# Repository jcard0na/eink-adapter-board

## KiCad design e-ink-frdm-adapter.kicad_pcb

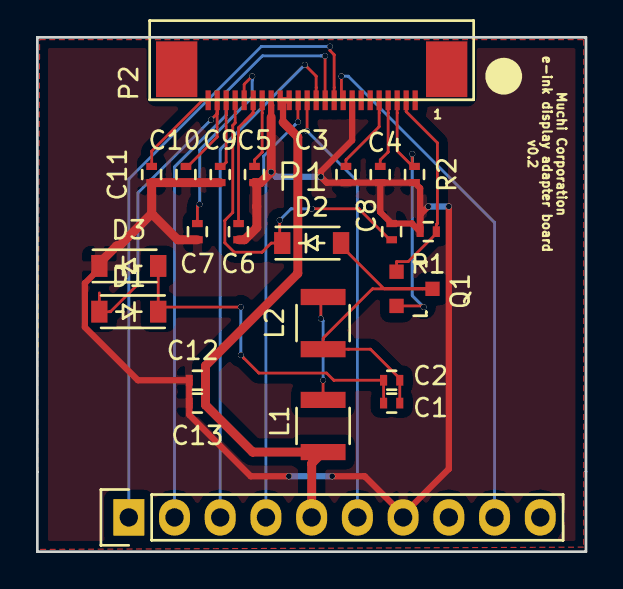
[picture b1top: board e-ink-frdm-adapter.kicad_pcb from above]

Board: 2 copper layers, 30.5 x 28.6 mm, 23 parts (0 on the bottom side), 22 nets.

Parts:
C1, C2, C3, C4, C5, C6, C7, C8, C9, C10, C11, C12, C13: MF-CAP-0402-1uF; R_0402
D1, D2, D3: MF-DIO-SOD123-BAT42; SOD-123
L1, L2: MF-IND-1210-10uH; R_1210
P1: 2-1734839-4; TE-2-1734592-4-bottom_contact
P2: 68000-110HLF; Pin_Header_Straight_1x10
Q1: MF-DSC-SOT233-BSS138; SOT-23
R1: MF-RES-0402-10K; R_0402
R2: MF-RES-0402-0; R_0402

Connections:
/BUSY: P1.9, P2.9
/CS: P1.12, P2.3
/D/~C: P1.11, P2.2
/GDR: P1.2, Q1.1, R1.1
/PREVGH: C8.1, D2.1, P1.21
/PREVGL: C10.1, D1.2, P1.23
/RESE: P1.3, Q1.2, R2.1
/SCLK: P1.13, P2.6
/SDI: P1.14, P2.4
/V3.3: C12.1, C13.1, L1.2, P1.15, P1.16, P2.5
/~RESET: P1.10, P2.1
GND: C3.1, C4.2, C5.2, C6.2, C7.2, C8.2, C9.2, C10.2, C11.2, C12.2, C13.2, D3.1, P1.8, P1.17, P2.7, R1.2, R2.2
unnamed: C1.1, C2.1, D1.1, D3.2
unnamed: C1.2, C2.2, D2.2, L2.1, Q1.3
unnamed: C3.2, P1.5
unnamed: C4.1, P1.4
unnamed: C5.1, P1.18
unnamed: C6.1, P1.19
unnamed: C7.1, P1.20
unnamed: C9.1, P1.22
unnamed: C11.1, P1.24
unnamed: L1.1, L2.2

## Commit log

2016-07-16 Regen netlist
2016-07-16 These files should be ignored
2016-08-12 Use bottom contact FPC conn footprint
2016-08-15 1. P1 FPC connector changed from top contact to bottom contact. 2. C2, C13 reduced from 1uF to 0.1uF 3. C1, C12 need not be installed (DNI) 4. R2 from 0 OHM to 10 OHM
2016-08-15 Regenerate with latest changes
2016-09-19 Updated to kicad 4.0.4 stable
2016-09-19 Remove rescue library uglyness
2016-09-19 Use house part for pin header
